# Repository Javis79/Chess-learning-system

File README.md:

# System Nauki Gry w Szachy

## Opis Projektu

System nauki gry w szachy jest dedykowany dla początkujących szachistów, którzy chcą poprawić swoje umiejętności i poznać zasady gry. Projekt oparty jest na mikrokontrolerze STM32, który zarządza interakcją z użytkownikiem oraz prezentuje ruchy na szachownicy.

Projekt ma na celu pomoc w nauce poprzez wizualne wskazywanie odpowiednich pól szachownicy oraz wyświetlanie notacji ruchów na wyświetlaczu 2.8 cala z interfejsem SPI. System wykorzystuje matrycę LED do podświetlania odpowiednich pól oraz umożliwia łatwe śledzenie postępów w grze.

## Zawartość Projektu

1. **Szachownica LED**: Matryca LED podświetlająca odpowiednie pola na planszy szachowej.
2. **Notacja Ruchów**: Wyświetlanie ruchów w odpowiedniej notacji na wyświetlaczu 2.8 cala z SPI.
3. **Mikrokontroler STM32**: Centralny układ sterujący systemem, odpowiedzialny za obsługę wyświetlacza i matrycy LED.
4. **Potencjalny Rozwój**:

   * **Wykrywanie Poprawności Ruchów**: Każde pole szachownicy będzie traktowane jako przycisk, a system będzie rozpoznawał odkliknięcie klawisza w celu sprawdzenia poprawności ruchu.
   * **Zegar Szachowy**: Wyświetlanie zegara szachowego na wyświetlaczu 2.8 cala, umożliwiającego śledzenie czasu każdej ze stron.

## Wymagania Systemowe

* **Mikrokontroler**: STM32F401RE ARM Cortex M4
* **Matryca LED**: 8x8 
* **Wyświetlacz**: 2.8 cala SPI
* **Zasilanie**: 5V 
* **Oprogramowanie**: STM32CubeIDE

## Wykorzystane Technologie

* **Mikrokontroler STM32**: Platforma sprzętowa do realizacji projektu.
* **SPI**: Interfejs do komunikacji z wyświetlaczem.
* **Matryca LED**: Wyświetlanie pól szachowych i interakcja z użytkownikiem.
* **C**: Język programowania do realizacji logiki sterującej mikrokontrolerem.

## Autor

Praca inżynierska jest tworzona przez Krystiana Bajerskiego, studenta elektroniki na AGH pod przewodnictwem dr inż. Agnieszki Dąbrowskiej-Boruch.

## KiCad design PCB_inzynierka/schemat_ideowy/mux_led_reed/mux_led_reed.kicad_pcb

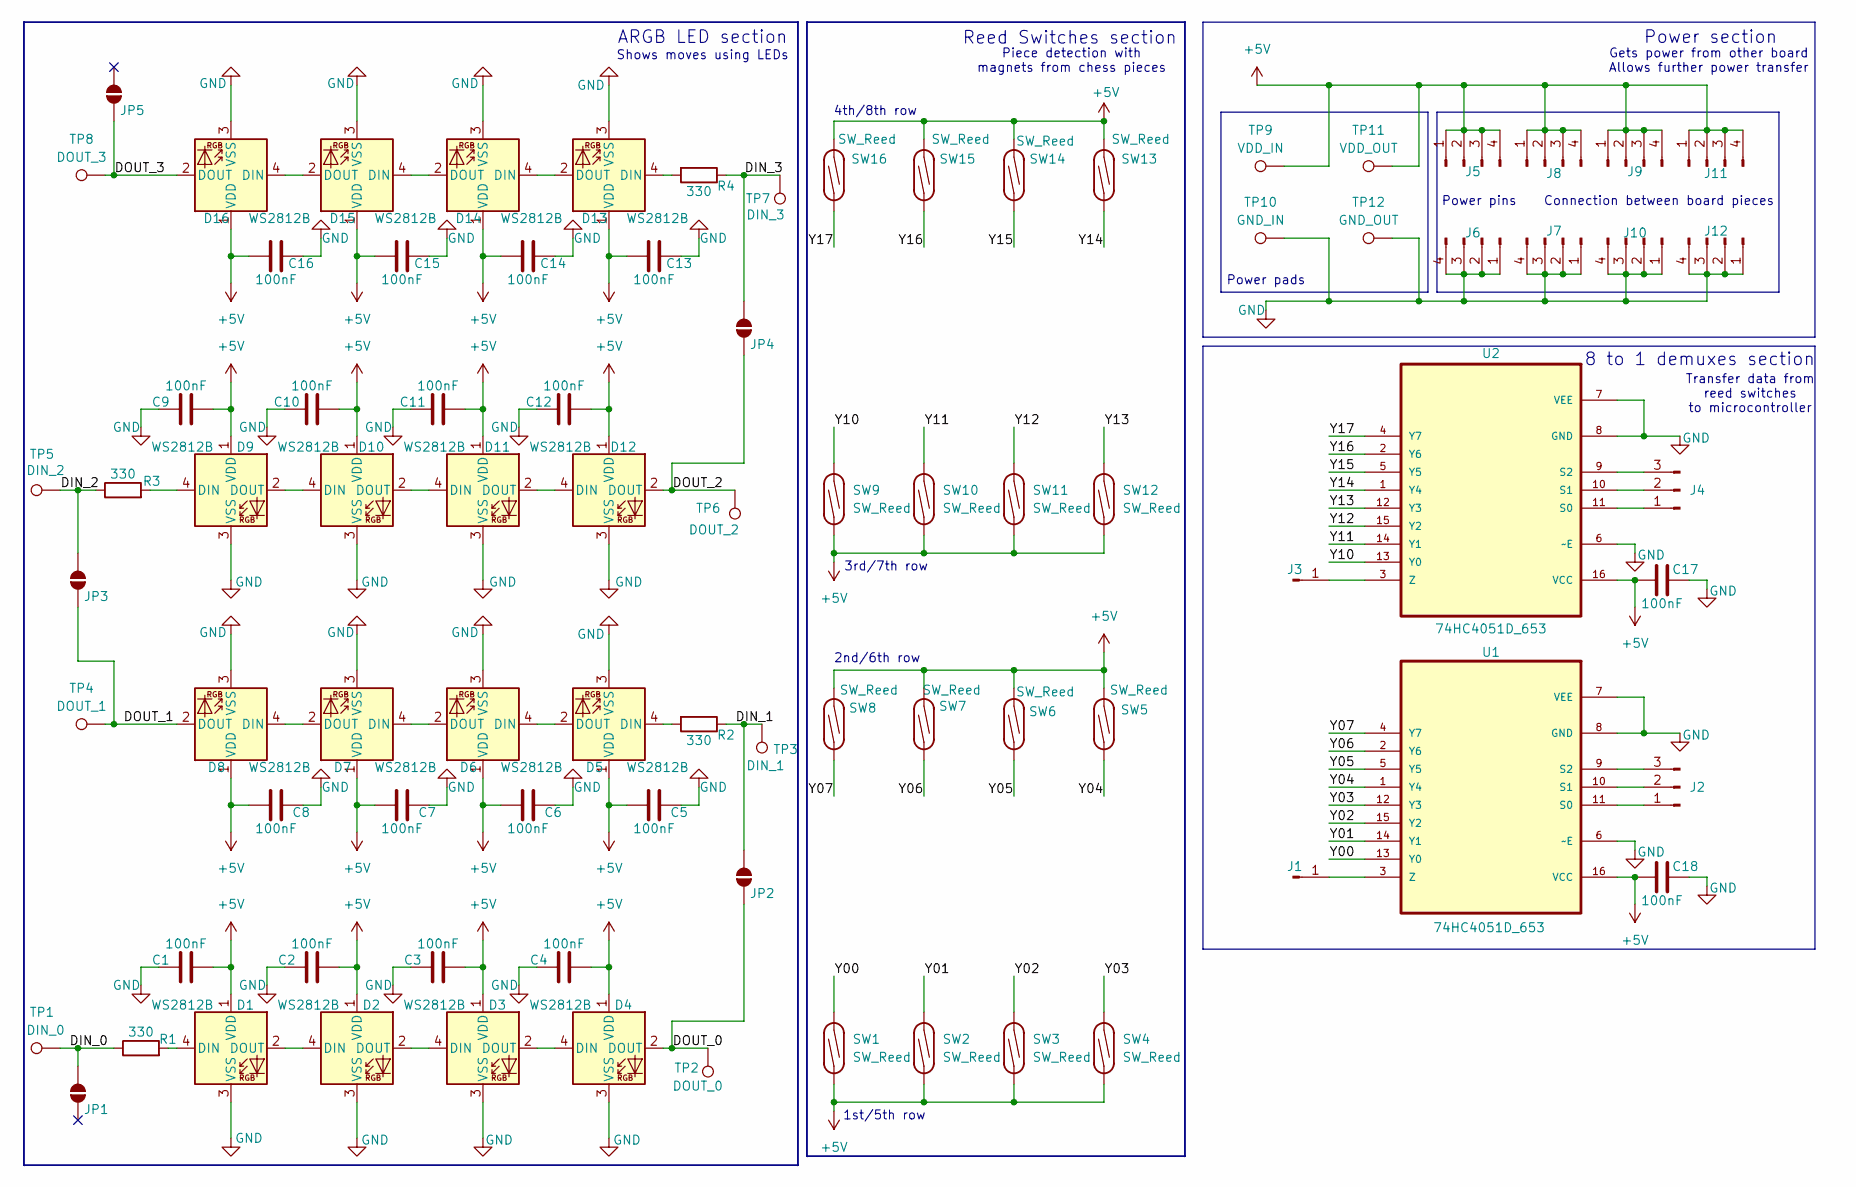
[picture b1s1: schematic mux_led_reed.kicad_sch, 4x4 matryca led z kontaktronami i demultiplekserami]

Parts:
C1, C2, C3, C4, C5, C6, C7, C8, C9, C10, C11, C12, C13, C14, C15, C16, C17, C18: 100nF; C_0805_2012Metric_Pad1.18x1.45mm_HandSolder
D1, D2, D3, D4, D5, D6, D7, D8, D9, D10, D11, D12, D13, D14, D15, D16: WS2812B; LED_WS2812B_PLCC4_5.0x5.0mm_P3.2mm
J1, J3: Conn_01x01_Pin; PinHeader_1x01_P2.54mm_Vertical
J2, J4: Conn_01x03_Pin; PinHeader_1x03_P2.54mm_Vertical
J5, J6, J9, J10: Conn_01x04_Pin; PinHeader_1x04_P2.54mm_Horizontal
J7, J8, J11, J12: Conn_01x04_Pin; PinSocket_1x04_P2.54mm_Horizontal
JP1, JP2, JP3, JP4, JP5: SolderJumper_2_Open; SolderJumper-2_P1.3mm_Open_Pad1.0x1.5mm
R1, R2, R3, R4: 330; R_0805_2012Metric_Pad1.20x1.40mm_HandSolder
SW1, SW2, SW3, SW4, SW5, SW6, SW7, SW8, SW9, SW10, SW11, SW12, SW13, SW14, SW15, SW16: SW_Reed; ReedSwitch_2x14mm
TP1: DIN_0; TestPoint_Pad_3.0x3.0mm
TP2: DOUT_0; TestPoint_Pad_3.0x3.0mm
TP3: DIN_1; TestPoint_Pad_3.0x3.0mm
TP4: DOUT_1; TestPoint_Pad_3.0x3.0mm
TP5: DIN_2; TestPoint_Pad_3.0x3.0mm
TP6: DOUT_2; TestPoint_Pad_3.0x3.0mm
TP7: DIN_3; TestPoint_Pad_3.0x3.0mm
TP8: DOUT_3; TestPoint_Pad_3.0x3.0mm
TP9: VDD_IN; TestPoint_Pad_4.0x4.0mm
TP10: GND_IN; TestPoint_Pad_4.0x4.0mm
TP11: VDD_OUT; TestPoint_Pad_4.0x4.0mm
TP12: GND_OUT; TestPoint_Pad_4.0x4.0mm
U1, U2: 74HC4051D_653; SOIC127P600X175-16N; MPN 74HC4051D,653

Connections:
+5V: C1.2, C2.2, C3.2, C4.2, C5.2, C6.2, C7.2, C8.2, C9.2, C10.2, C11.2, C12.2, C13.2, C14.2, C15.2, C16.2, C17.1, C18.1, D1.1 (VDD), D2.1 (VDD), D3.1 (VDD), D4.1 (VDD), D5.1 (VDD), D6.1 (VDD), D7.1 (VDD), D8.1 (VDD), D9.1 (VDD), D10.1 (VDD), D11.1 (VDD), D12.1 (VDD), D13.1 (VDD), D14.1 (VDD), D15.1 (VDD), D16.1 (VDD), J5.1, J5.2, J5.3, J5.4, J8.1, J8.2, J8.3, J8.4, J9.1, J9.2, J9.3, J9.4, J11.1, J11.2, J11.3, J11.4, SW1.2, SW2.2, SW3.2, SW4.2, SW5.2, SW6.2, SW7.2, SW8.2, SW9.2, SW10.2, SW11.2, SW12.2, SW13.2, SW14.2, SW15.2, SW16.2, TP9.1, TP11.1, U1.16 (VCC), U2.16 (VCC)
/DIN_0: JP1.2 (B), R1.1, TP1.1
/DIN_1: JP2.2 (B), R2.1, TP3.1
/DIN_2: JP3.2 (B), R3.1, TP5.1
/DIN_3: JP4.2 (B), R4.1, TP7.1
/DOUT_0: D4.2 (DOUT), JP2.1 (A), TP2.1
/DOUT_1: D8.2 (DOUT), JP3.1 (A), TP4.1
/DOUT_2: D12.2 (DOUT), JP4.1 (A), TP6.1
/DOUT_3: D16.2 (DOUT), JP5.1 (A), TP8.1
/Y00: SW1.1, U1.13 (Y0)
/Y01: SW2.1, U1.14 (Y1)
/Y02: SW3.1, U1.15 (Y2)
/Y03: SW4.1, U1.12 (Y3)
/Y04: SW5.1, U1.1 (Y4)
/Y05: SW6.1, U1.5 (Y5)
/Y06: SW7.1, U1.2 (Y6)
/Y07: SW8.1, U1.4 (Y7)
/Y10: SW9.1, U2.13 (Y0)
/Y11: SW10.1, U2.14 (Y1)
/Y12: SW11.1, U2.15 (Y2)
/Y13: SW12.1, U2.12 (Y3)
/Y14: SW13.1, U2.1 (Y4)
/Y15: SW14.1, U2.5 (Y5)
/Y16: SW15.1, U2.2 (Y6)
/Y17: SW16.1, U2.4 (Y7)
GND: C1.1, C2.1, C3.1, C4.1, C5.1, C6.1, C7.1, C8.1, C9.1, C10.1, C11.1, C12.1, C13.1, C14.1, C15.1, C16.1, C17.2, C18.2, D1.3 (VSS), D2.3 (VSS), D3.3 (VSS), D4.3 (VSS), D5.3 (VSS), D6.3 (VSS), D7.3 (VSS), D8.3 (VSS), D9.3 (VSS), D10.3 (VSS), D11.3 (VSS), D12.3 (VSS), D13.3 (VSS), D14.3 (VSS), D15.3 (VSS), D16.3 (VSS), J6.1, J6.2, J6.3, J6.4, J7.1, J7.2, J7.3, J7.4, J10.1, J10.2, J10.3, J10.4, J12.1, J12.2, J12.3, J12.4, TP10.1, TP12.1, U1.6 (~E), U1.7 (VEE), U1.8 (GND), U2.6 (~E), U2.7 (VEE), U2.8 (GND)
unnamed: D1.4 (DIN), R1.2
unnamed: D1.2 (DOUT), D2.4 (DIN)
unnamed: D2.2 (DOUT), D3.4 (DIN)
unnamed: D3.2 (DOUT), D4.4 (DIN)
unnamed: D5.4 (DIN), R2.2
unnamed: D5.2 (DOUT), D6.4 (DIN)
unnamed: D6.2 (DOUT), D7.4 (DIN)
unnamed: D7.2 (DOUT), D8.4 (DIN)
unnamed: D9.4 (DIN), R3.2
unnamed: D9.2 (DOUT), D10.4 (DIN)
unnamed: D10.2 (DOUT), D11.4 (DIN)
unnamed: D11.2 (DOUT), D12.4 (DIN)
unnamed: D13.4 (DIN), R4.2
unnamed: D13.2 (DOUT), D14.4 (DIN)
unnamed: D14.2 (DOUT), D15.4 (DIN)
unnamed: D15.2 (DOUT), D16.4 (DIN)
unnamed: J1.1, U1.3 (Z)
unnamed: J2.1, U1.11 (S0)
unnamed: J2.2, U1.10 (S1)
unnamed: J2.3, U1.9 (S2)
unnamed: J3.1, U2.3 (Z)
unnamed: J4.1, U2.11 (S0)
unnamed: J4.2, U2.10 (S1)
unnamed: J4.3, U2.9 (S2)

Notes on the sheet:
ARGB LED section
Gets power from other board Allows further power transfer
2nd/6th row
Shows moves using LEDs
1st/5th row
Power pads
Power section
8 to 1 demuxes section
Reed Switches section
Power pins Connection between board pieces
Piece detection with magnets from chess pieces
4th/8th row
Transfer data from reed switches to microcontroller
3rd/7th row

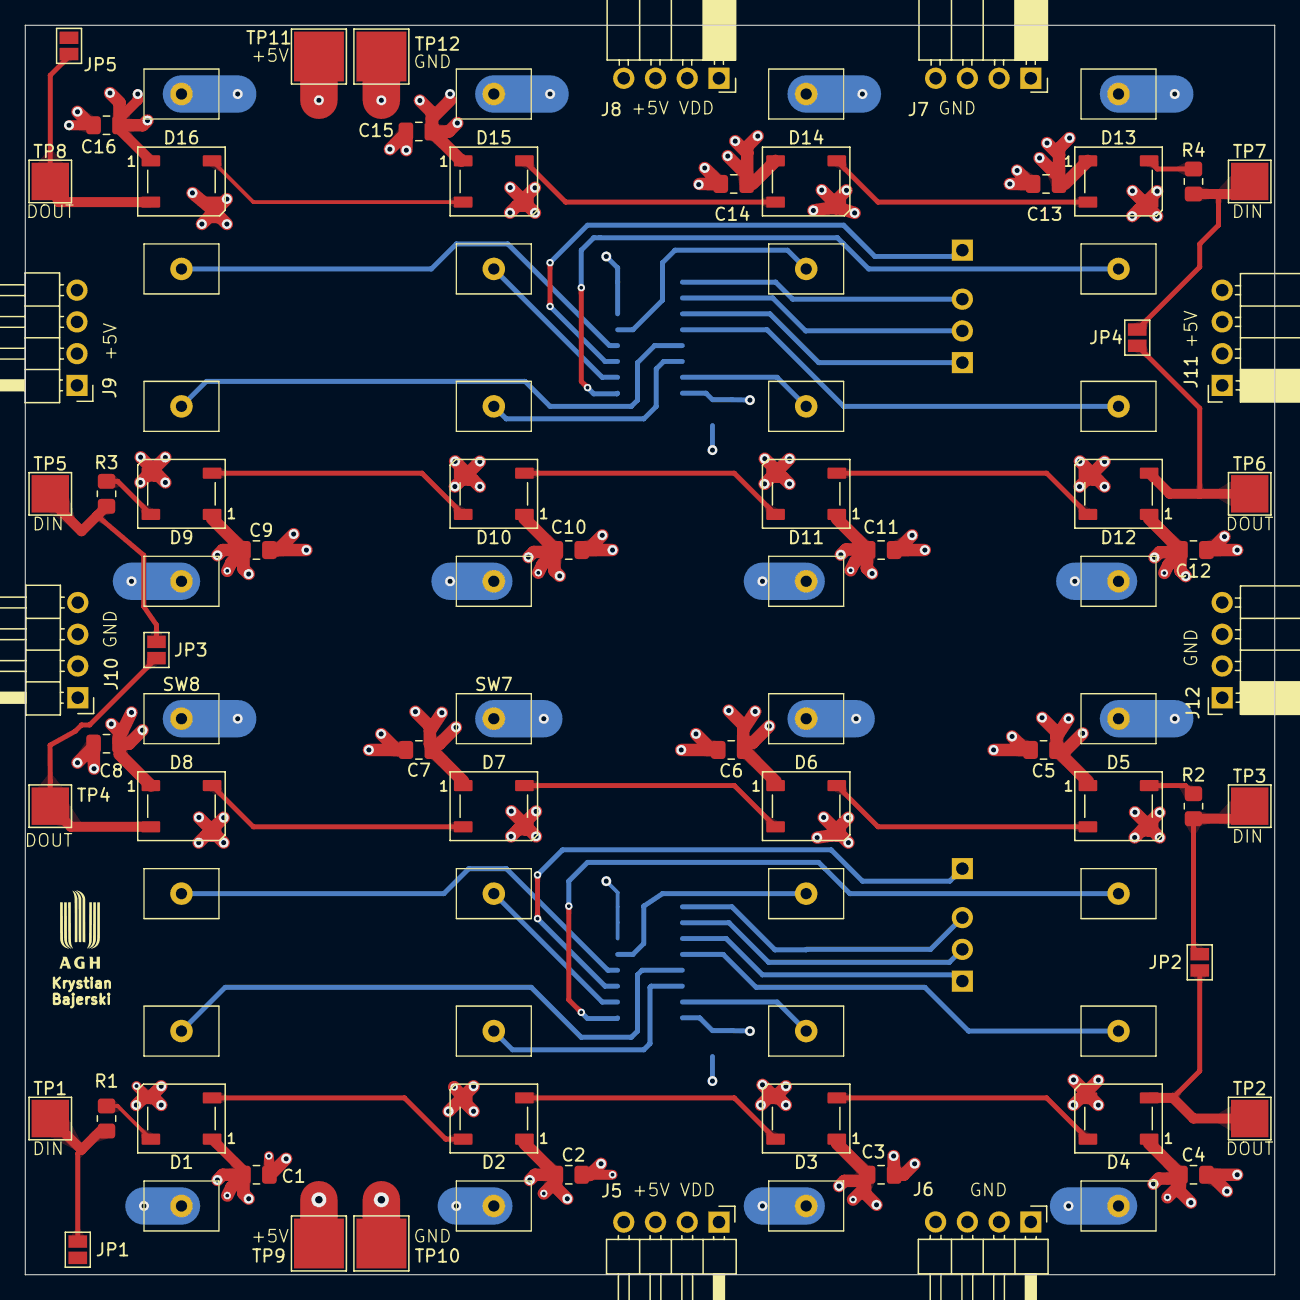
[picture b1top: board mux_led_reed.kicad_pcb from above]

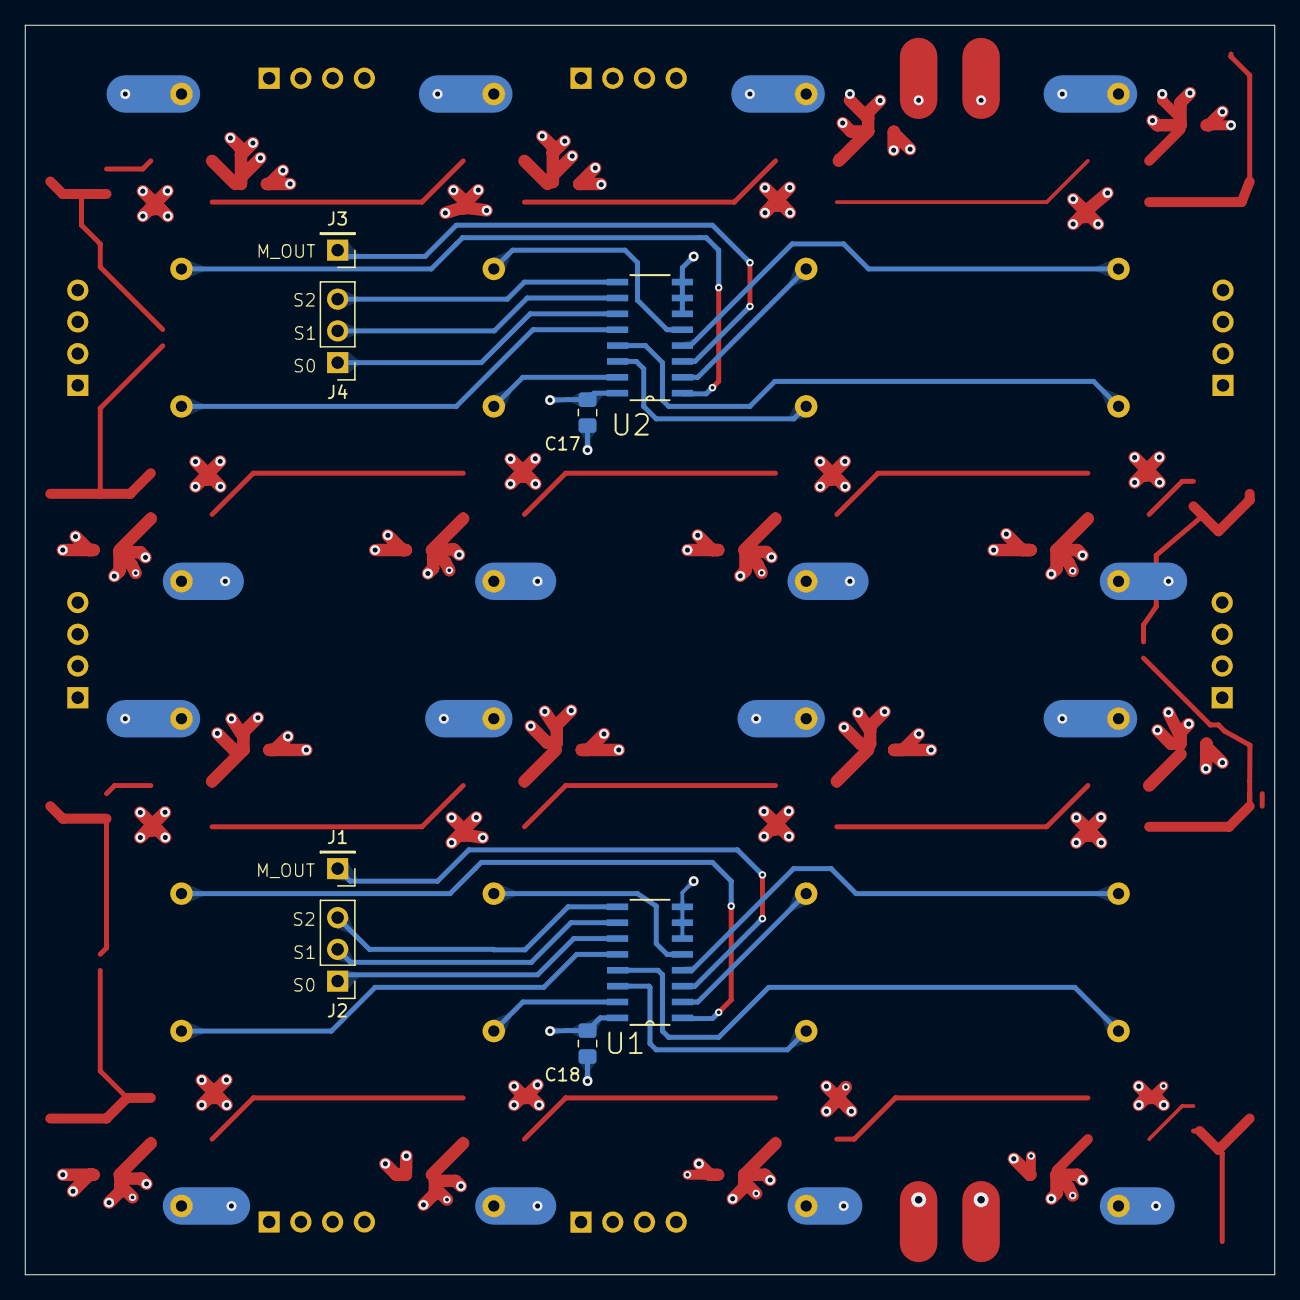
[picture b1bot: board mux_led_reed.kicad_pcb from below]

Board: 4 copper layers, 100.0 x 100.0 mm, 85 parts (8 on the bottom side), 50 nets.

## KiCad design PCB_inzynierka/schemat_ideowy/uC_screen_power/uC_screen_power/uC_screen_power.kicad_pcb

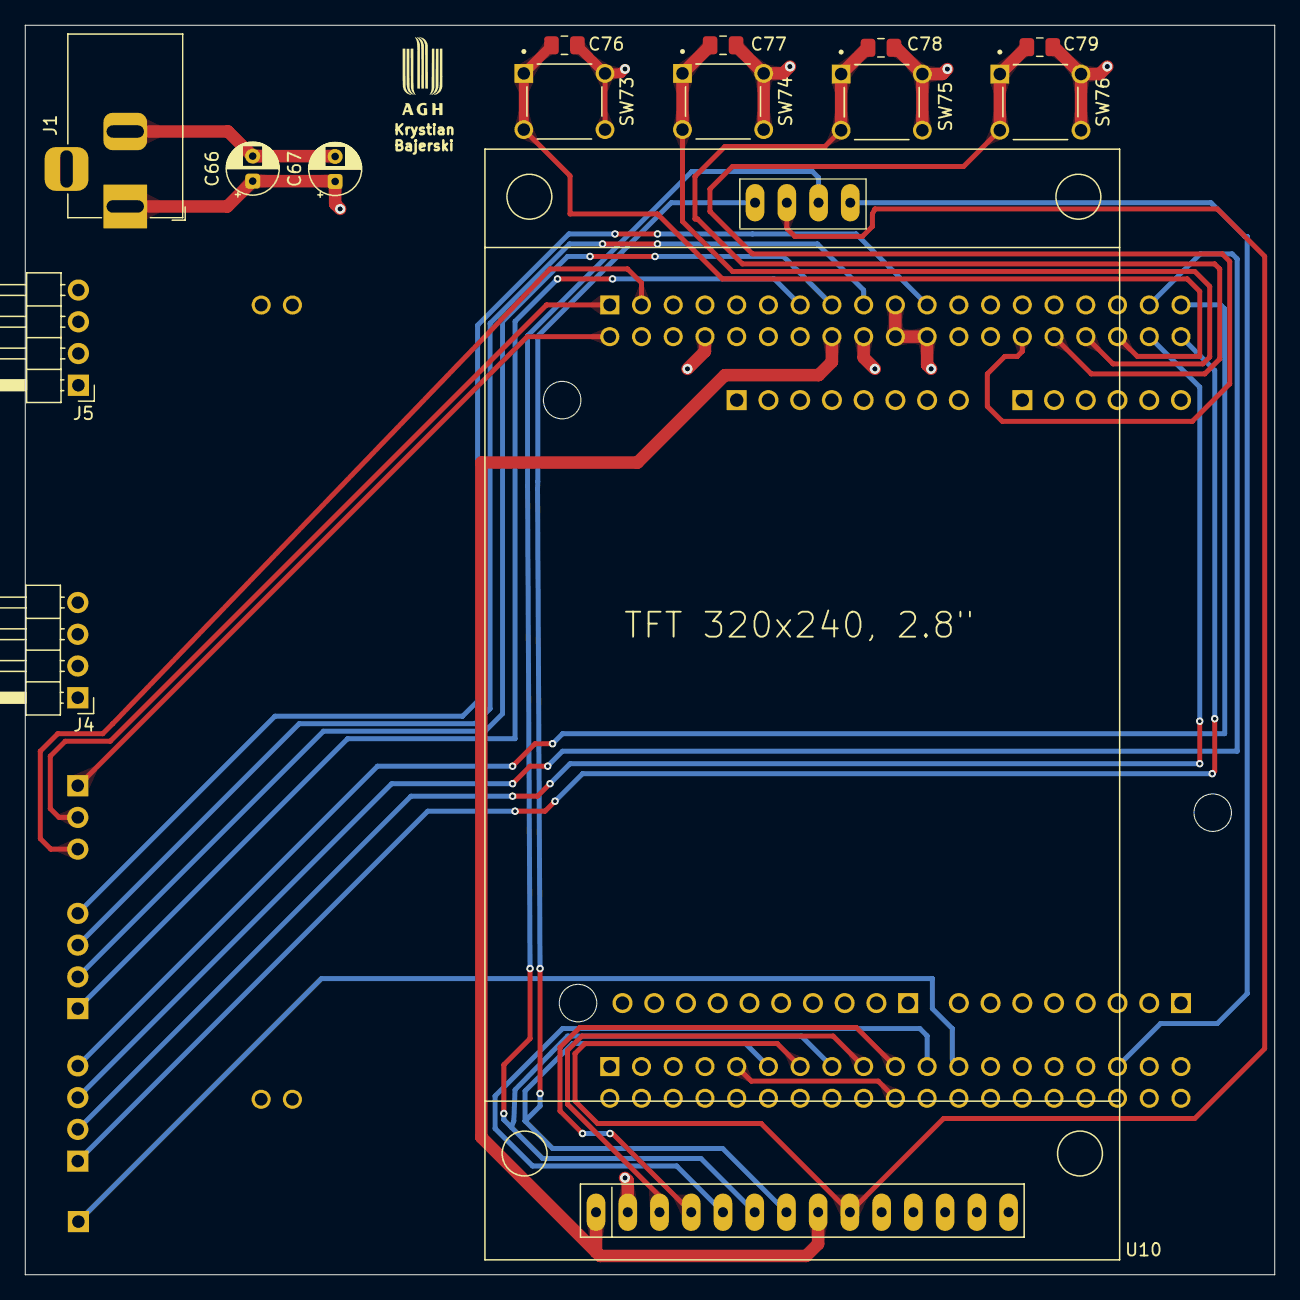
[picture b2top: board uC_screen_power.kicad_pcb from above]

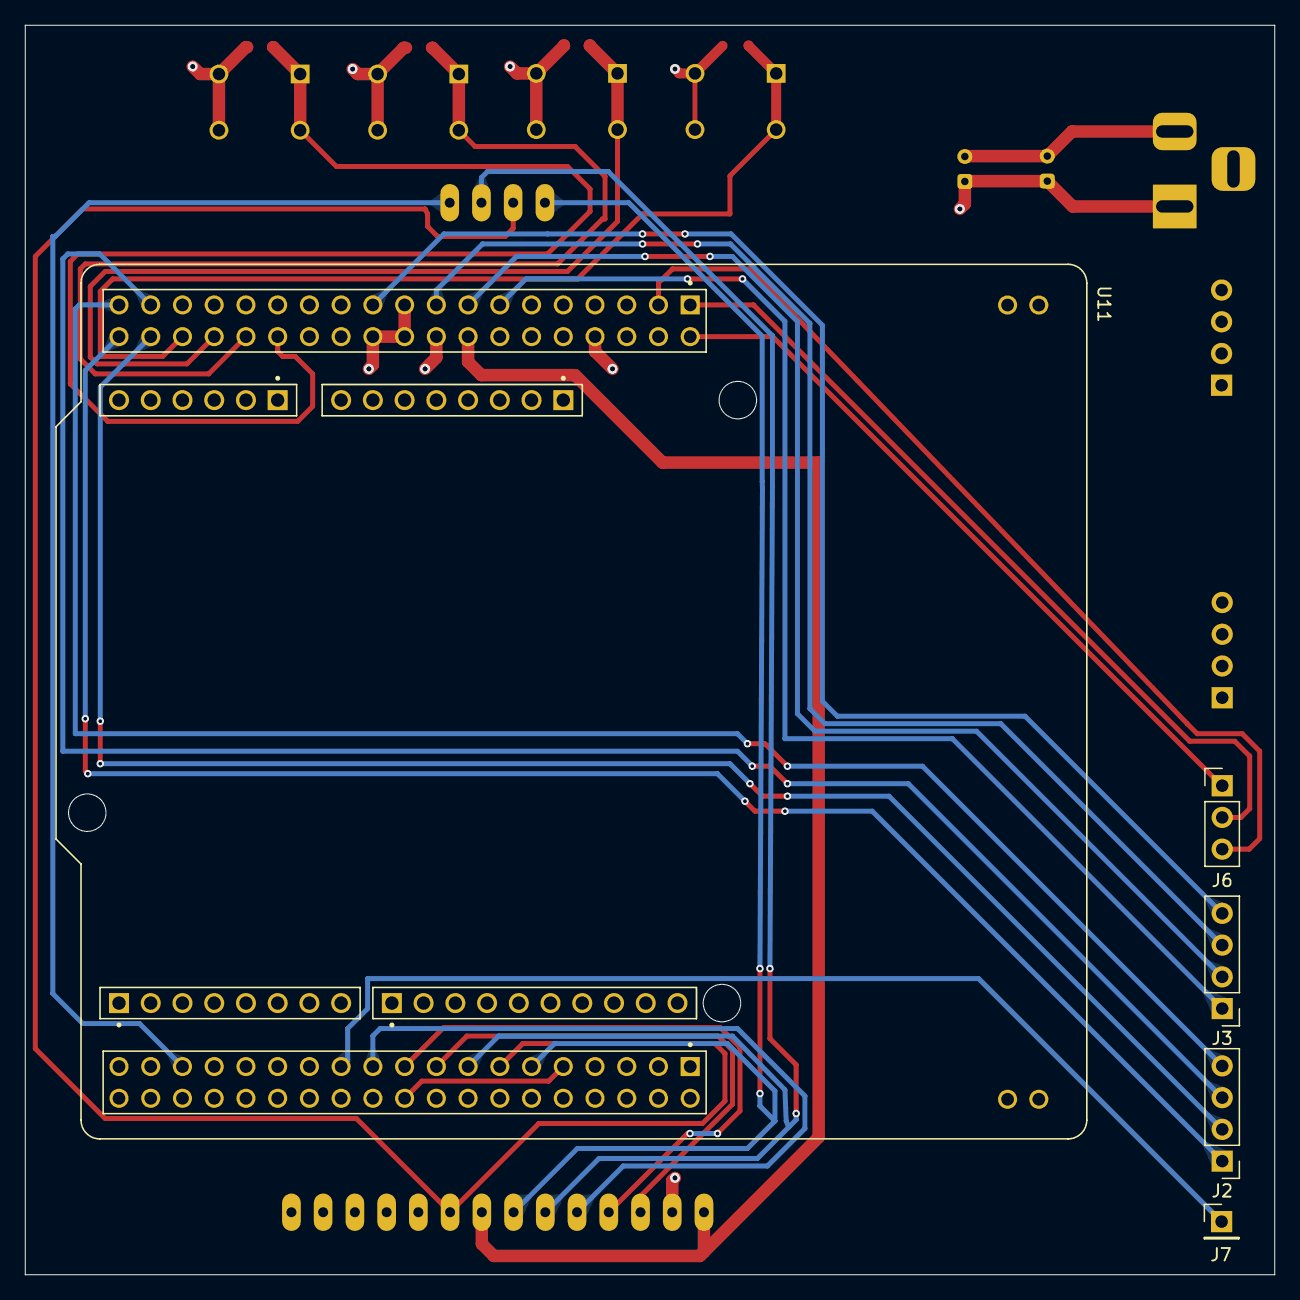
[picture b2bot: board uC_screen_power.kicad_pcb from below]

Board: 4 copper layers, 100.0 x 100.0 mm, 19 parts (5 on the bottom side), 27 nets.

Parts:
C66: 22uF; CP_Radial_D4.0mm_P2.00mm
C67: 100nF; CP_Radial_D4.0mm_P2.00mm
C76, C77, C78, C79: 100nF; C_0805_2012Metric_Pad1.18x1.45mm_HandSolder
J1: Barrel_Jack_Switch; BarrelJack_Horizontal
J2, J3: Conn_01x04_Pin; PinHeader_1x04_P2.54mm_Vertical
J4, J5: Conn_01x04_Pin; PinHeader_1x04_P2.54mm_Horizontal
J6: Conn_01x03_Pin; PinHeader_1x03_P2.54mm_Vertical
J7: Conn_01x01_Pin; PinHeader_1x01_P2.54mm_Vertical
SW73, SW74, SW75, SW76: SW_DPST; SW_TS02-66-60-BK-100-LCR-D
U10: TFT_320x240; TFT-320x240
U11: NUCLEO-F401RE; ST_NUCLEO-F401RE

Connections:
+5V: C66.1, C67.1, J1.1, J5.1, J5.2, J5.3, J5.4, U11.7_18 (+5V_S1)
/CS: U10.3 (CS), U11.10_17 (PB6)
/CS_SD: U10.18 (SD_CS), U11.10_33 (PA10)
/DC: U10.5 (DC), U11.10_21 (PA9)
/LED_OUT: J7.1, U11.10_23 (PA8)
/MISO: U10.9 (MISO), U10.16 (SD_MISO), U11.10_13 (PA6)
/MOSI: U10.6 (MOSI), U10.17 (SD_MOSI), U11.10_15 (PA7)
/MUX_OUT_0: J2.1, U11.7_38 (PC0/PB8)
/MUX_OUT_1: J2.2, U11.7_36 (PC1/PB9)
/MUX_OUT_2: J2.3, U11.7_35 (PC2)
/MUX_OUT_3: J2.4, U11.7_37 (PC3)
/MUX_OUT_4: J3.4, U11.7_21 (PB7)
/MUX_OUT_5: J3.1, U11.7_13 (PA13)
/MUX_OUT_6: J3.2, U11.7_15 (PA14)
/MUX_OUT_7: J3.3, U11.7_17 (PA15)
/RST: U10.4 (RST), U11.10_19 (PC7)
/S0: J6.2, U11.7_1 (PC10)
/S1: J6.1, U11.7_2 (PC11)
/S2: J6.3, U11.7_3 (PC12)
/SCK: U10.7 (SCK), U10.15 (SD_SCK), U11.10_11 (PA5)
/SW1: C76.1, SW73.1, SW73.3, U11.7_34 (PB0)
/SW2: C77.1, SW74.1, SW74.3, U11.7_32 (PA4)
/SW3: C78.1, SW75.1, SW75.3, U11.7_30 (PA1)
/SW4: C79.1, SW76.1, SW76.3, U11.7_28 (PA0)
/VDD: U10.1 (VCC), U10.8 (LED), U11.7_16 (+3V3_S1)
GND: C66.2, C67.2, C76.2, C77.2, C78.2, C79.2, J1.2, J4.1, J4.2, J4.3, J4.4, SW73.2, SW73.4, SW74.2, SW74.4, SW75.2, SW75.4, SW76.2, SW76.4, U10.2 (GND), U11.7_8 (GND_S1), U11.7_19 (GND_S1), U11.7_20 (GND_S1), U11.7_22 (GND_S1)
unnamed: U11.10_9 (GND_S2), U11.10_20 (GND_S2)

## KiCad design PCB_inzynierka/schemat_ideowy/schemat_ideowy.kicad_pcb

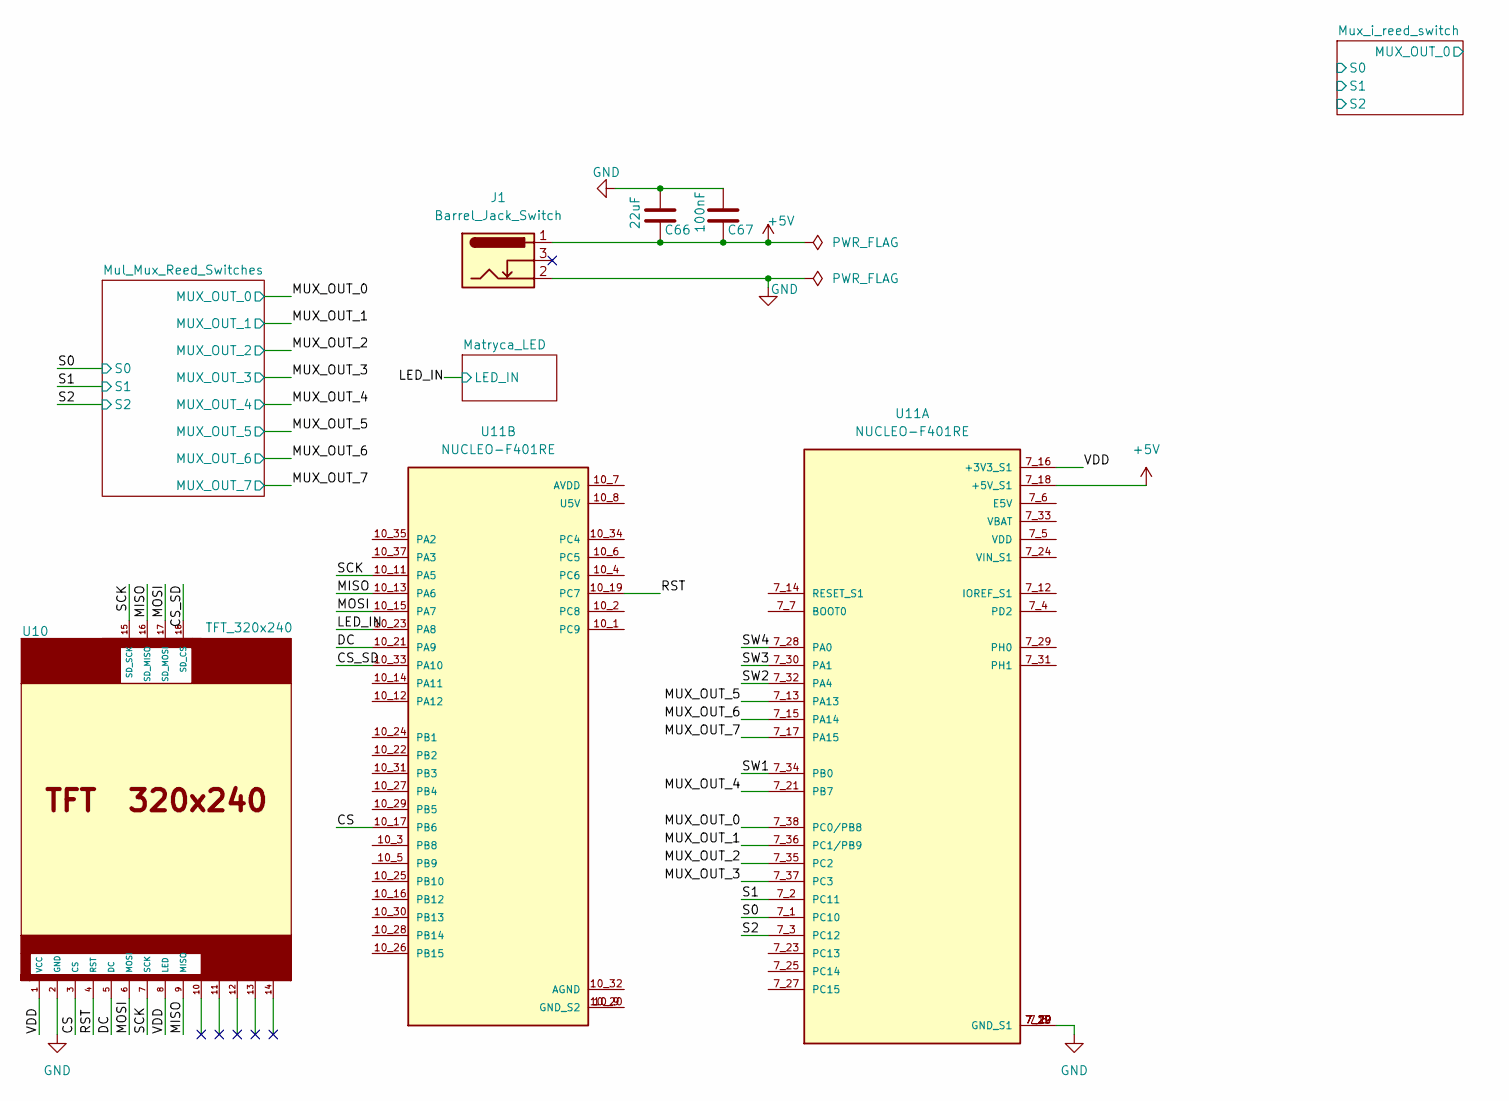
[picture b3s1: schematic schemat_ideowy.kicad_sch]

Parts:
C66: 22uF; CP_Radial_D4.0mm_P2.00mm
C67: 100nF; CP_Radial_D4.0mm_P2.00mm
J1: Barrel_Jack_Switch; BarrelJack_Horizontal
U10: TFT_320x240; TFT-320x240
U11: NUCLEO-F401RE; ST_NUCLEO-F401RE; PARTREV 13

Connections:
+5V: C66.2, C67.2, J1.1, U11.7_18 (+5V_S1); also elsewhere on the board
/CS: U10.3 (CS), U11.10_17 (PB6)
/CS_SD: U10.18 (SD_CS), U11.10_33 (PA10)
/DC: U10.5 (DC), U11.10_21 (PA9)
/LED_IN: U11.10_23 (PA8); also elsewhere on the board
/MISO: U10.9 (MISO), U10.16 (SD_MISO), U11.10_13 (PA6)
/MOSI: U10.6 (MOSI), U10.17 (SD_MOSI), U11.10_15 (PA7)
/MUX_OUT_0: U11.7_38 (PC0/PB8); also elsewhere on the board
/MUX_OUT_1: U11.7_36 (PC1/PB9); also elsewhere on the board
/MUX_OUT_2: U11.7_35 (PC2); also elsewhere on the board
/MUX_OUT_3: U11.7_37 (PC3); also elsewhere on the board
/MUX_OUT_4: U11.7_21 (PB7); also elsewhere on the board
/MUX_OUT_5: U11.7_13 (PA13); also elsewhere on the board
/MUX_OUT_6: U11.7_15 (PA14); also elsewhere on the board
/MUX_OUT_7: U11.7_17 (PA15); also elsewhere on the board
/RST: U10.4 (RST), U11.10_19 (PC7)
/S0: U11.7_1 (PC10); also elsewhere on the board
/S1: U11.7_2 (PC11); also elsewhere on the board
/S2: U11.7_3 (PC12); also elsewhere on the board
/SCK: U10.7 (SCK), U10.15 (SD_SCK), U11.10_11 (PA5)
/SW1: U11.7_34 (PB0)
/SW2: U11.7_32 (PA4)
/SW3: U11.7_30 (PA1)
/SW4: U11.7_28 (PA0)
/VDD: U10.1 (VCC), U10.8 (LED), U11.7_16 (+3V3_S1)
GND: C66.1, C67.1, J1.2, U10.2 (GND), U11.7_8 (GND_S1), U11.7_19 (GND_S1), U11.7_20 (GND_S1), U11.7_22 (GND_S1); also elsewhere on the board
unnamed: U11.10_9 (GND_S2), U11.10_20 (GND_S2)

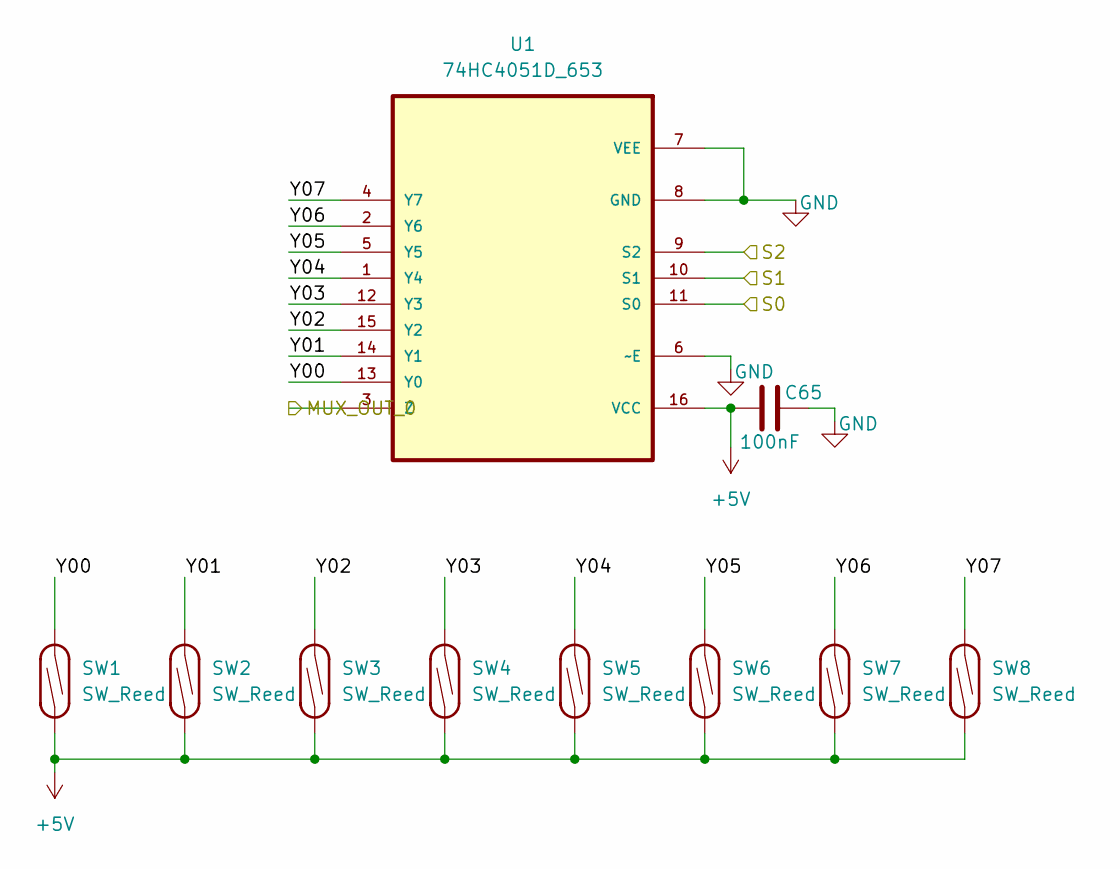
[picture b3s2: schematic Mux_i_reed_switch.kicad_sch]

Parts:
C65: 100nF; C_0805_2012Metric_Pad1.18x1.45mm_HandSolder
SW1, SW2, SW3, SW4, SW5, SW6, SW7, SW8: SW_Reed; ReedSwitch_2x14mm
U1: 74HC4051D_653; SOIC127P600X175-16N; MPN 74HC4051D,653

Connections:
+5V: C65.1, SW1.2, SW2.2, SW3.2, SW4.2, SW5.2, SW6.2, SW7.2, SW8.2, U1.16 (VCC); also elsewhere on the board
/Mux_i_reed_switch/MUX_OUT_0: U1.3 (Z)
/Mux_i_reed_switch/S0: U1.11 (S0)
/Mux_i_reed_switch/S1: U1.10 (S1)
/Mux_i_reed_switch/S2: U1.9 (S2)
/Mux_i_reed_switch/Y00: SW1.1, U1.13 (Y0)
/Mux_i_reed_switch/Y01: SW2.1, U1.14 (Y1)
/Mux_i_reed_switch/Y02: SW3.1, U1.15 (Y2)
/Mux_i_reed_switch/Y03: SW4.1, U1.12 (Y3)
/Mux_i_reed_switch/Y04: SW5.1, U1.1 (Y4)
/Mux_i_reed_switch/Y05: SW6.1, U1.5 (Y5)
/Mux_i_reed_switch/Y06: SW7.1, U1.2 (Y6)
/Mux_i_reed_switch/Y07: SW8.1, U1.4 (Y7)
GND: C65.2, U1.6 (~E), U1.7 (VEE), U1.8 (GND); also elsewhere on the board

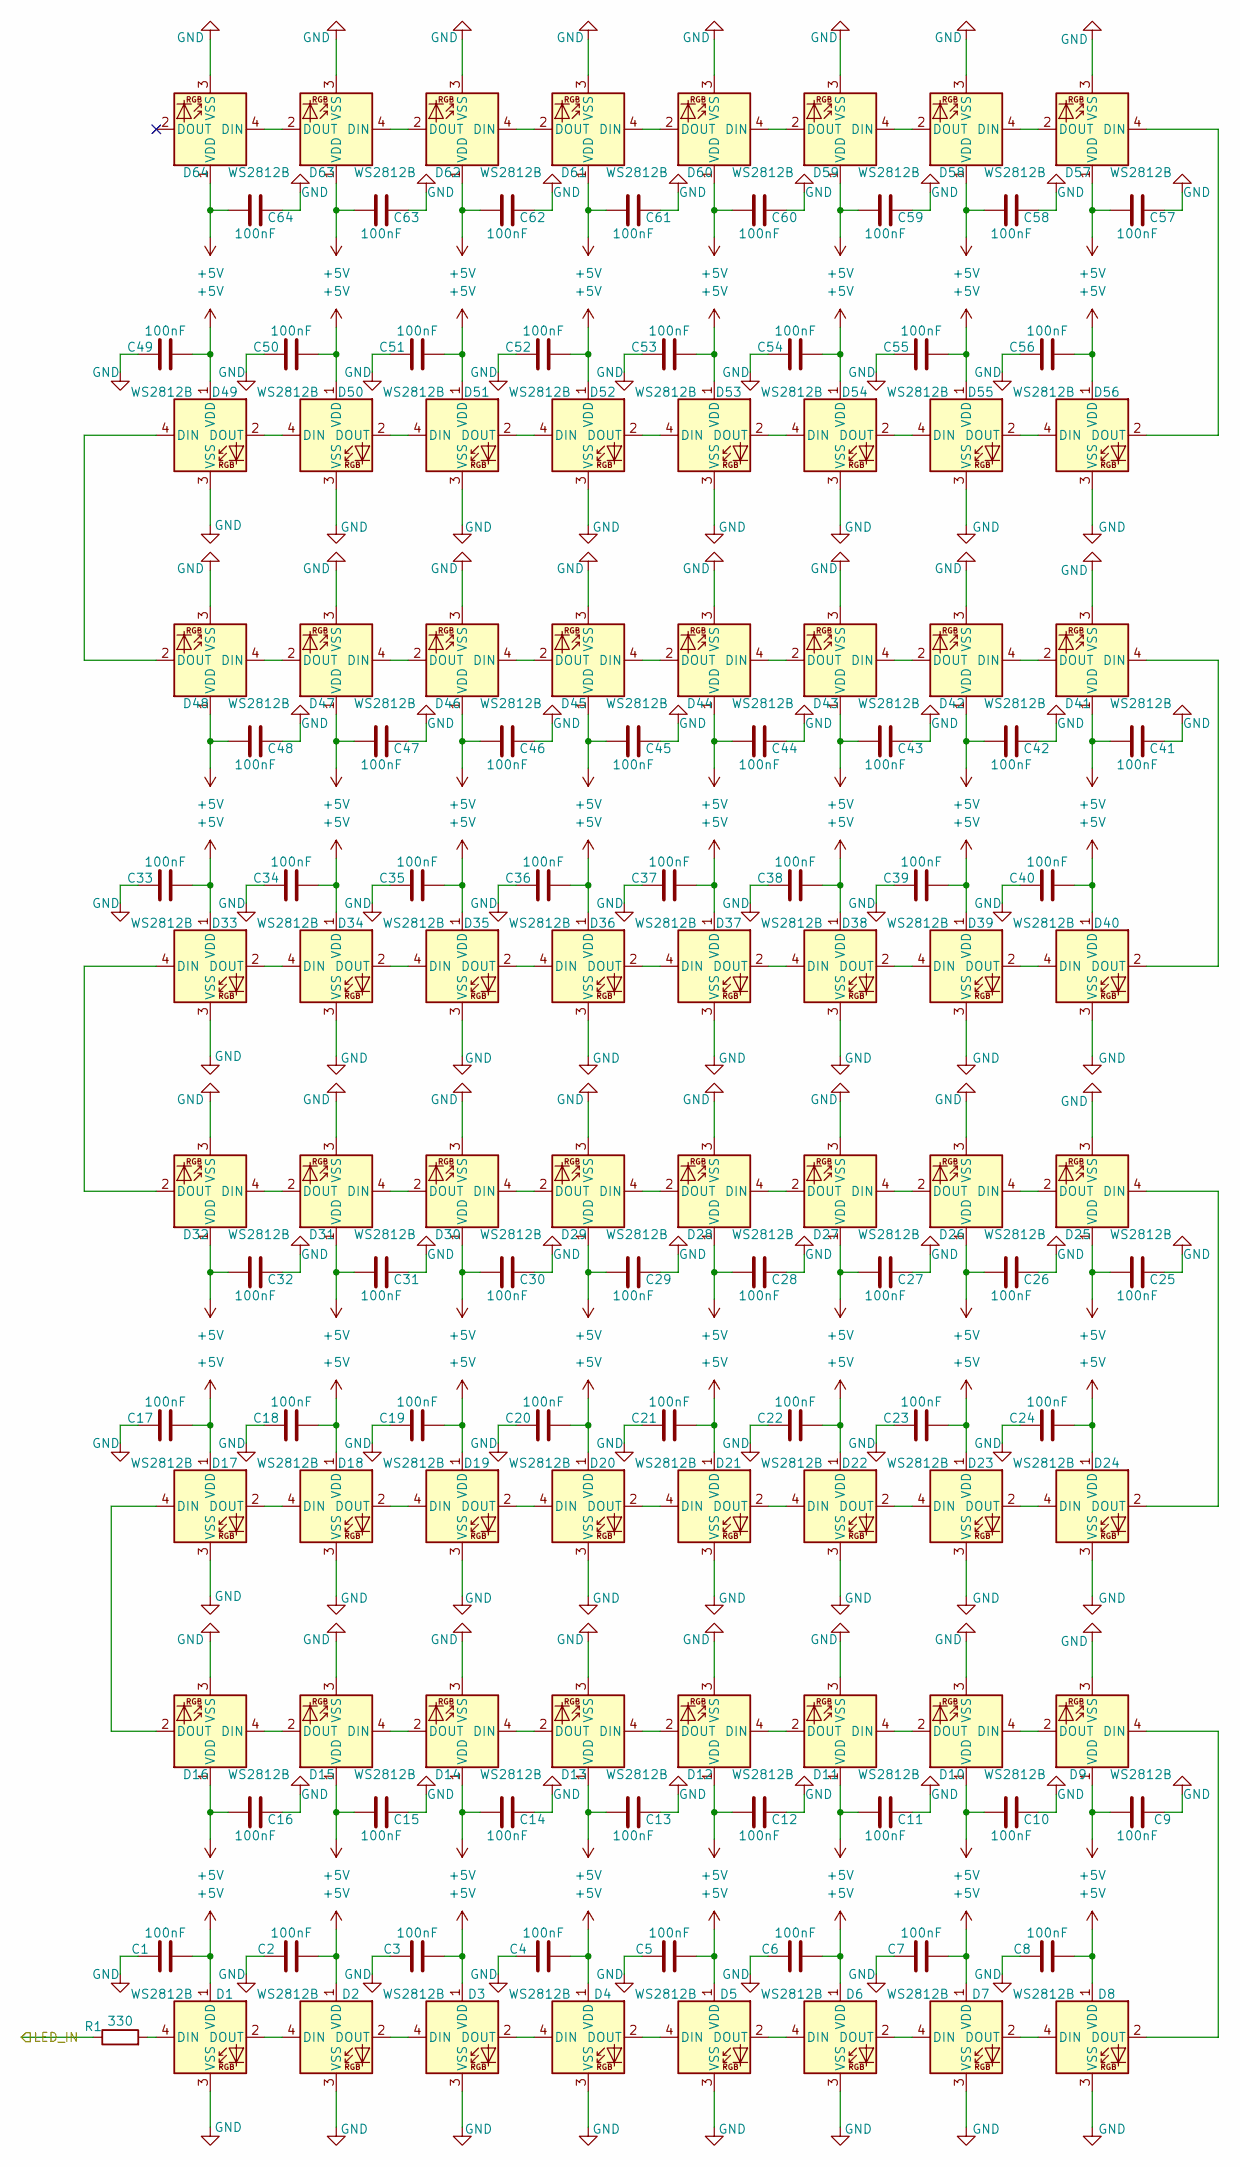
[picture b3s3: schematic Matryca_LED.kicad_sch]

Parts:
C1, C2, C3, C4, C5, C6, C7, C8, C9, C10, C11, C12, C13, C14, C15, C16, C17, C18, C19, C20, C21, C22, C23, C24, C25, C26, C27, C28, C29, C30, C31, C32, C33, C34, C35, C36, C37, C38, C39, C40, C41, C42, C43, C44, C45, C46, C47, C48, C49, C50, C51, C52, C53, C54, C55, C56, C57, C58, C59, C60, C61, C62, C63, C64: 100nF; C_0805_2012Metric_Pad1.18x1.45mm_HandSolder
D1, D2, D3, D4, D5, D6, D7, D8, D9, D10, D11, D12, D13, D14, D15, D16, D17, D18, D19, D20, D21, D22, D23, D24, D25, D26, D27, D28, D29, D30, D31, D32, D33, D34, D35, D36, D37, D38, D39, D40, D41, D42, D43, D44, D45, D46, D47, D48, D49, D50, D51, D52, D53, D54, D55, D56, D57, D58, D59, D60, D61, D62, D63, D64: WS2812B; LED_WS2812B_PLCC4_5.0x5.0mm_P3.2mm
R1: 330; R_0805_2012Metric_Pad1.20x1.40mm_HandSolder

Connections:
+5V: C1.2, C2.2, C3.2, C4.2, C5.2, C6.2, C7.2, C8.2, C9.2, C10.2, C11.2, C12.2, C13.2, C14.2, C15.2, C16.2, C17.2, C18.2, C19.2, C20.2, C21.2, C22.2, C23.2, C24.2, C25.2, C26.2, C27.2, C28.2, C29.2, C30.2, C31.2, C32.2, C33.2, C34.2, C35.2, C36.2, C37.2, C38.2, C39.2, C40.2, C41.2, C42.2, C43.2, C44.2, C45.2, C46.2, C47.2, C48.2, C49.2, C50.2, C51.2, C52.2, C53.2, C54.2, C55.2, C56.2, C57.2, C58.2, C59.2, C60.2, C61.2, C62.2, C63.2, C64.2, D1.1 (VDD), D2.1 (VDD), D3.1 (VDD), D4.1 (VDD), D5.1 (VDD), D6.1 (VDD), D7.1 (VDD), D8.1 (VDD), D9.1 (VDD), D10.1 (VDD), D11.1 (VDD), D12.1 (VDD), D13.1 (VDD), D14.1 (VDD), D15.1 (VDD), D16.1 (VDD), D17.1 (VDD), D18.1 (VDD), D19.1 (VDD), D20.1 (VDD), D21.1 (VDD), D22.1 (VDD), D23.1 (VDD), D24.1 (VDD), D25.1 (VDD), D26.1 (VDD), D27.1 (VDD), D28.1 (VDD), D29.1 (VDD), D30.1 (VDD), D31.1 (VDD), D32.1 (VDD), D33.1 (VDD), D34.1 (VDD), D35.1 (VDD), D36.1 (VDD), D37.1 (VDD), D38.1 (VDD), D39.1 (VDD), D40.1 (VDD), D41.1 (VDD), D42.1 (VDD), D43.1 (VDD), D44.1 (VDD), D45.1 (VDD), D46.1 (VDD), D47.1 (VDD), D48.1 (VDD), D49.1 (VDD), D50.1 (VDD), D51.1 (VDD), D52.1 (VDD), D53.1 (VDD), D54.1 (VDD), D55.1 (VDD), D56.1 (VDD), D57.1 (VDD), D58.1 (VDD), D59.1 (VDD), D60.1 (VDD), D61.1 (VDD), D62.1 (VDD), D63.1 (VDD), D64.1 (VDD); also elsewhere on the board
/LED_IN: R1.1; also elsewhere on the board
GND: C1.1, C2.1, C3.1, C4.1, C5.1, C6.1, C7.1, C8.1, C9.1, C10.1, C11.1, C12.1, C13.1, C14.1, C15.1, C16.1, C17.1, C18.1, C19.1, C20.1, C21.1, C22.1, C23.1, C24.1, C25.1, C26.1, C27.1, C28.1, C29.1, C30.1, C31.1, C32.1, C33.1, C34.1, C35.1, C36.1, C37.1, C38.1, C39.1, C40.1, C41.1, C42.1, C43.1, C44.1, C45.1, C46.1, C47.1, C48.1, C49.1, C50.1, C51.1, C52.1, C53.1, C54.1, C55.1, C56.1, C57.1, C58.1, C59.1, C60.1, C61.1, C62.1, C63.1, C64.1, D1.3 (VSS), D2.3 (VSS), D3.3 (VSS), D4.3 (VSS), D5.3 (VSS), D6.3 (VSS), D7.3 (VSS), D8.3 (VSS), D9.3 (VSS), D10.3 (VSS), D11.3 (VSS), D12.3 (VSS), D13.3 (VSS), D14.3 (VSS), D15.3 (VSS), D16.3 (VSS), D17.3 (VSS), D18.3 (VSS), D19.3 (VSS), D20.3 (VSS), D21.3 (VSS), D22.3 (VSS), D23.3 (VSS), D24.3 (VSS), D25.3 (VSS), D26.3 (VSS), D27.3 (VSS), D28.3 (VSS), D29.3 (VSS), D30.3 (VSS), D31.3 (VSS), D32.3 (VSS), D33.3 (VSS), D34.3 (VSS), D35.3 (VSS), D36.3 (VSS), D37.3 (VSS), D38.3 (VSS), D39.3 (VSS), D40.3 (VSS), D41.3 (VSS), D42.3 (VSS), D43.3 (VSS), D44.3 (VSS), D45.3 (VSS), D46.3 (VSS), D47.3 (VSS), D48.3 (VSS), D49.3 (VSS), D50.3 (VSS), D51.3 (VSS), D52.3 (VSS), D53.3 (VSS), D54.3 (VSS), D55.3 (VSS), D56.3 (VSS), D57.3 (VSS), D58.3 (VSS), D59.3 (VSS), D60.3 (VSS), D61.3 (VSS), D62.3 (VSS), D63.3 (VSS), D64.3 (VSS); also elsewhere on the board
unnamed: D1.4 (DIN), R1.2
unnamed: D1.2 (DOUT), D2.4 (DIN)
unnamed: D2.2 (DOUT), D3.4 (DIN)
unnamed: D3.2 (DOUT), D4.4 (DIN)
unnamed: D4.2 (DOUT), D5.4 (DIN)
unnamed: D5.2 (DOUT), D6.4 (DIN)
unnamed: D6.2 (DOUT), D7.4 (DIN)
unnamed: D7.2 (DOUT), D8.4 (DIN)
unnamed: D8.2 (DOUT), D9.4 (DIN)
unnamed: D9.2 (DOUT), D10.4 (DIN)
unnamed: D10.2 (DOUT), D11.4 (DIN)
unnamed: D11.2 (DOUT), D12.4 (DIN)
unnamed: D12.2 (DOUT), D13.4 (DIN)
unnamed: D13.2 (DOUT), D14.4 (DIN)
unnamed: D14.2 (DOUT), D15.4 (DIN)
unnamed: D15.2 (DOUT), D16.4 (DIN)
unnamed: D16.2 (DOUT), D17.4 (DIN)
unnamed: D17.2 (DOUT), D18.4 (DIN)
unnamed: D18.2 (DOUT), D19.4 (DIN)
unnamed: D19.2 (DOUT), D20.4 (DIN)
unnamed: D20.2 (DOUT), D21.4 (DIN)
unnamed: D21.2 (DOUT), D22.4 (DIN)
unnamed: D22.2 (DOUT), D23.4 (DIN)
unnamed: D23.2 (DOUT), D24.4 (DIN)
unnamed: D24.2 (DOUT), D25.4 (DIN)
unnamed: D25.2 (DOUT), D26.4 (DIN)
unnamed: D26.2 (DOUT), D27.4 (DIN)
unnamed: D27.2 (DOUT), D28.4 (DIN)
unnamed: D28.2 (DOUT), D29.4 (DIN)
unnamed: D29.2 (DOUT), D30.4 (DIN)
unnamed: D30.2 (DOUT), D31.4 (DIN)
unnamed: D31.2 (DOUT), D32.4 (DIN)
unnamed: D32.2 (DOUT), D33.4 (DIN)
unnamed: D33.2 (DOUT), D34.4 (DIN)
unnamed: D34.2 (DOUT), D35.4 (DIN)
unnamed: D35.2 (DOUT), D36.4 (DIN)
unnamed: D36.2 (DOUT), D37.4 (DIN)
unnamed: D37.2 (DOUT), D38.4 (DIN)
unnamed: D38.2 (DOUT), D39.4 (DIN)
unnamed: D39.2 (DOUT), D40.4 (DIN)
unnamed: D40.2 (DOUT), D41.4 (DIN)
unnamed: D41.2 (DOUT), D42.4 (DIN)
unnamed: D42.2 (DOUT), D43.4 (DIN)
unnamed: D43.2 (DOUT), D44.4 (DIN)
unnamed: D44.2 (DOUT), D45.4 (DIN)
unnamed: D45.2 (DOUT), D46.4 (DIN)
unnamed: D46.2 (DOUT), D47.4 (DIN)
unnamed: D47.2 (DOUT), D48.4 (DIN)
unnamed: D48.2 (DOUT), D49.4 (DIN)
unnamed: D49.2 (DOUT), D50.4 (DIN)
unnamed: D50.2 (DOUT), D51.4 (DIN)
unnamed: D51.2 (DOUT), D52.4 (DIN)
unnamed: D52.2 (DOUT), D53.4 (DIN)
unnamed: D53.2 (DOUT), D54.4 (DIN)
unnamed: D54.2 (DOUT), D55.4 (DIN)
unnamed: D55.2 (DOUT), D56.4 (DIN)
unnamed: D56.2 (DOUT), D57.4 (DIN)
unnamed: D57.2 (DOUT), D58.4 (DIN)
unnamed: D58.2 (DOUT), D59.4 (DIN)
unnamed: D59.2 (DOUT), D60.4 (DIN)
unnamed: D60.2 (DOUT), D61.4 (DIN)
unnamed: D61.2 (DOUT), D62.4 (DIN)
unnamed: D62.2 (DOUT), D63.4 (DIN)
unnamed: D63.2 (DOUT), D64.4 (DIN)
